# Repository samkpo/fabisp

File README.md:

# fabisp
FabISP

This project was taken from here: http://fab.cba.mit.edu/content/projects/fabisp/
All the credits belong to the original author.

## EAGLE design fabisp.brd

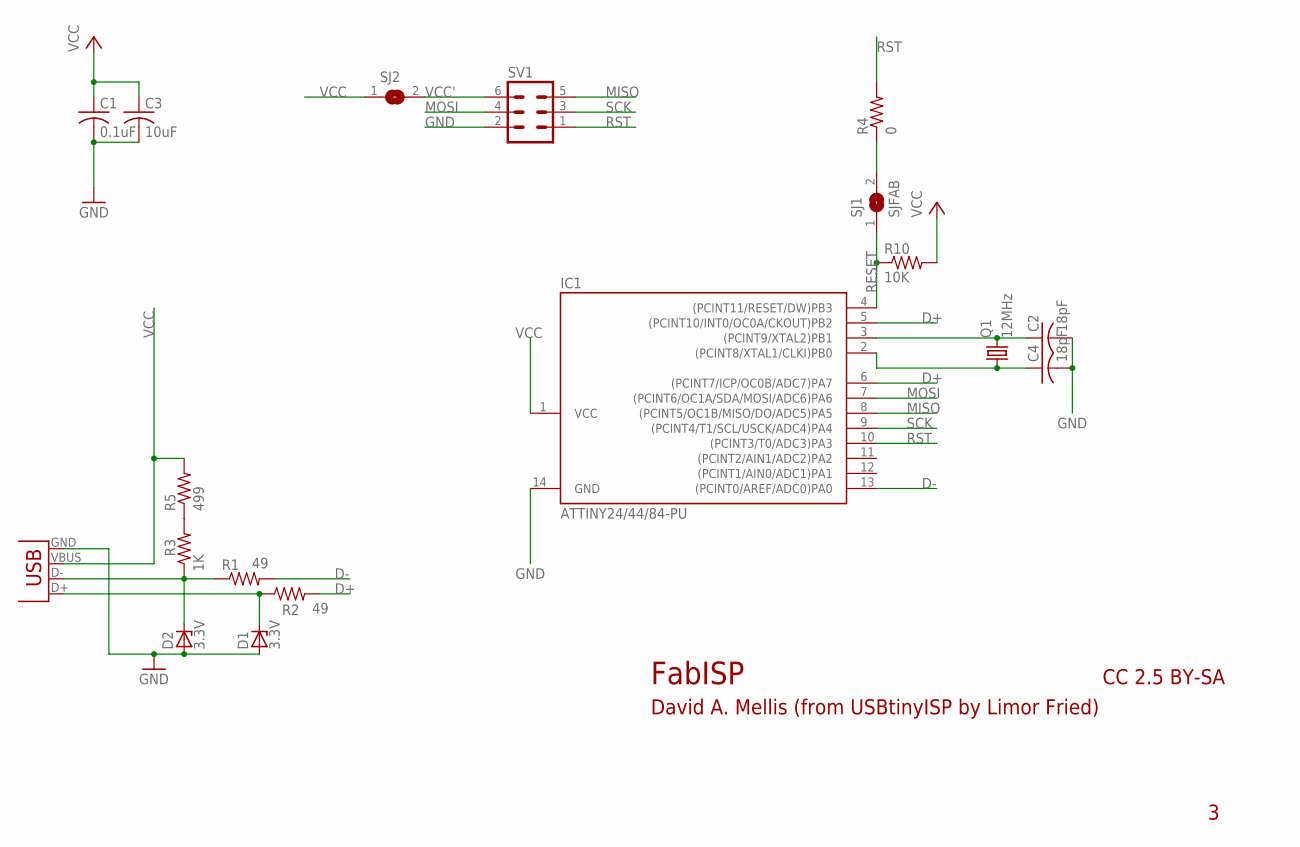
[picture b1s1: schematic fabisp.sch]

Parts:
C1: 0.1uF; C025-024X044
C2, C4: 18pF; C025-024X044
C3: 10uF; C025-024X044
D1, D2: 3.3V; DO41Z10
IC1: ATTINY24/44/84-PU; DIL14
Q1: 12MHz; HC49U-V
R1, R2: 49; 0204/7
R3: 1K; 0204/7
R4: 0; 0204/7
R5: 499; 0204/7
R10: 10K; 0204/7
SJ1, SJ2: SJFAB
SV1: MA03-2
X1: USB_MINIB

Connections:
D+: IC1.5 ((PCINT10/INT0/OC0A/CKOUT)PB2), IC1.6 ((PCINT7/ICP/OC0B/ADC7)PA7), R2.2
D-: IC1.13 ((PCINT0/AREF/ADC0)PA0), R1.2
GND: C1.2, C2.2, C3.2, C4.2, D1.A (ANODE), D2.A (ANODE), IC1.14 (GND), SV1.2, X1.GND
MISO: IC1.8 ((PCINT5/OC1B/MISO/DO/ADC5)PA5), SV1.5
MOSI: IC1.7 ((PCINT6/OC1A/SDA/MOSI/ADC6)PA6), SV1.4
unnamed: D2.C (CATHODE), R1.1, R3.1, X1.D-
unnamed: D1.C (CATHODE), R2.1, X1.D+
unnamed: R4.1, SJ1.2
unnamed: C4.1, IC1.2 ((PCINT8/XTAL1/CLKI)PB0), Q1.1
unnamed: C2.1, IC1.3 ((PCINT9/XTAL2)PB1), Q1.2
unnamed: R3.2, R5.1
RESET: IC1.4 ((PCINT11/RESET/DW)PB3), R10.1, SJ1.1
RST: IC1.10 ((PCINT3/T0/ADC3)PA3), R4.2, SV1.1
SCK: IC1.9 ((PCINT4/T1/SCL/USCK/ADC4)PA4), SV1.3
VCC: C1.1, C3.1, IC1.1 (VCC), R5.2, R10.2, SJ2.1, X1.VBUS
VCC': SJ2.2, SV1.6

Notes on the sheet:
FabISP
David A. Mellis (from USBtinyISP by Limor Fried)
CC 2.5 BY-SA

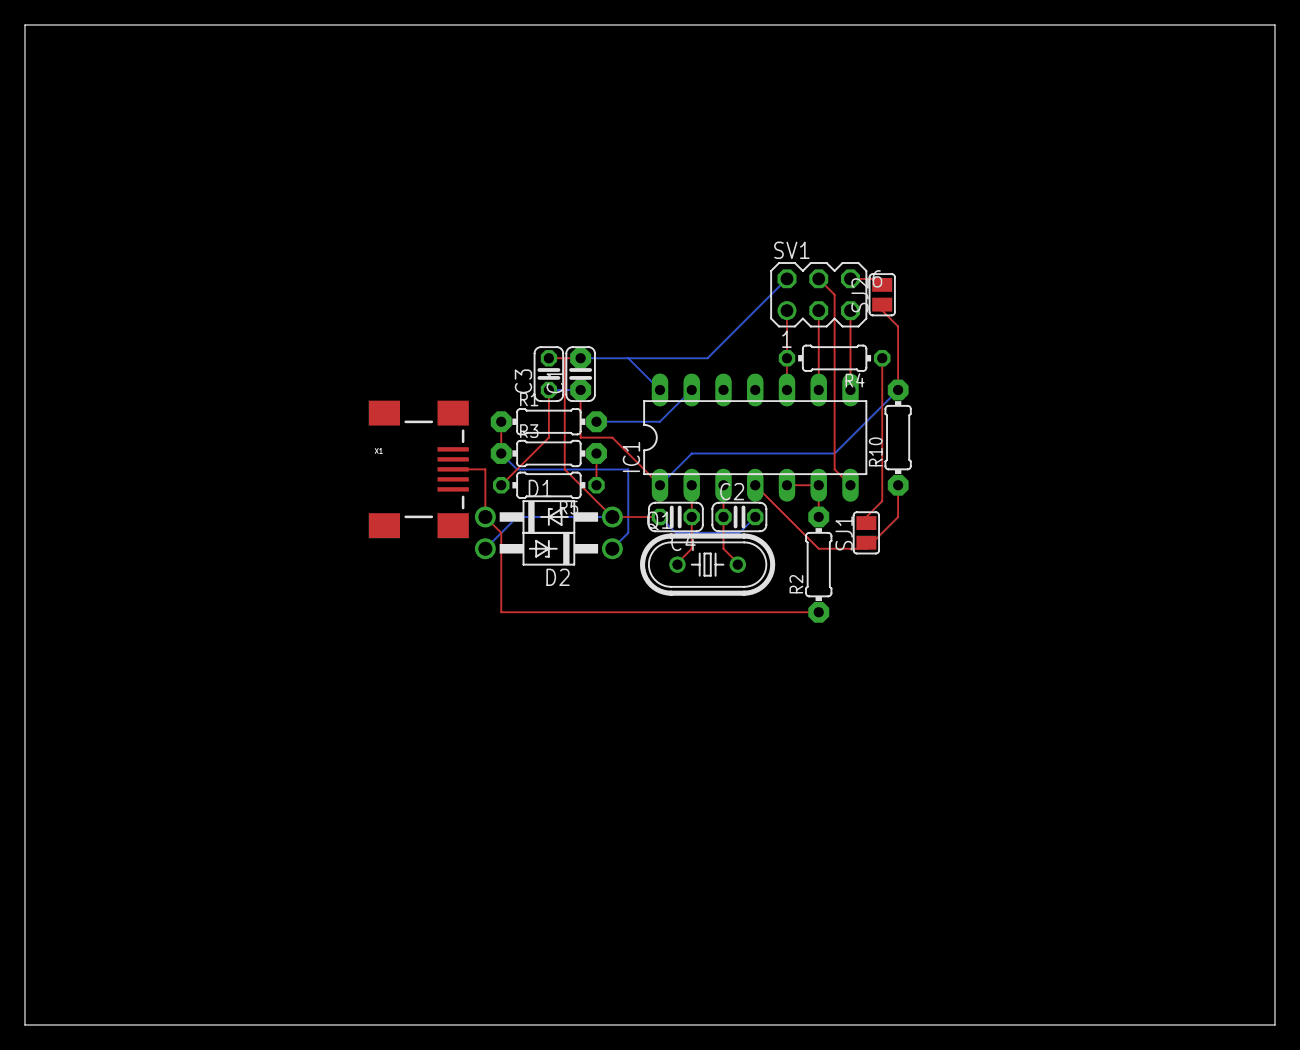
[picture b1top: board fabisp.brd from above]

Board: 2 copper layers, 100.0 x 80.0 mm, 18 parts (0 on the bottom side), 16 nets.

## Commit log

2015-01-10 Initial commit. Board taken from http://fab.cba.mit.edu/content/projects/fabisp/
